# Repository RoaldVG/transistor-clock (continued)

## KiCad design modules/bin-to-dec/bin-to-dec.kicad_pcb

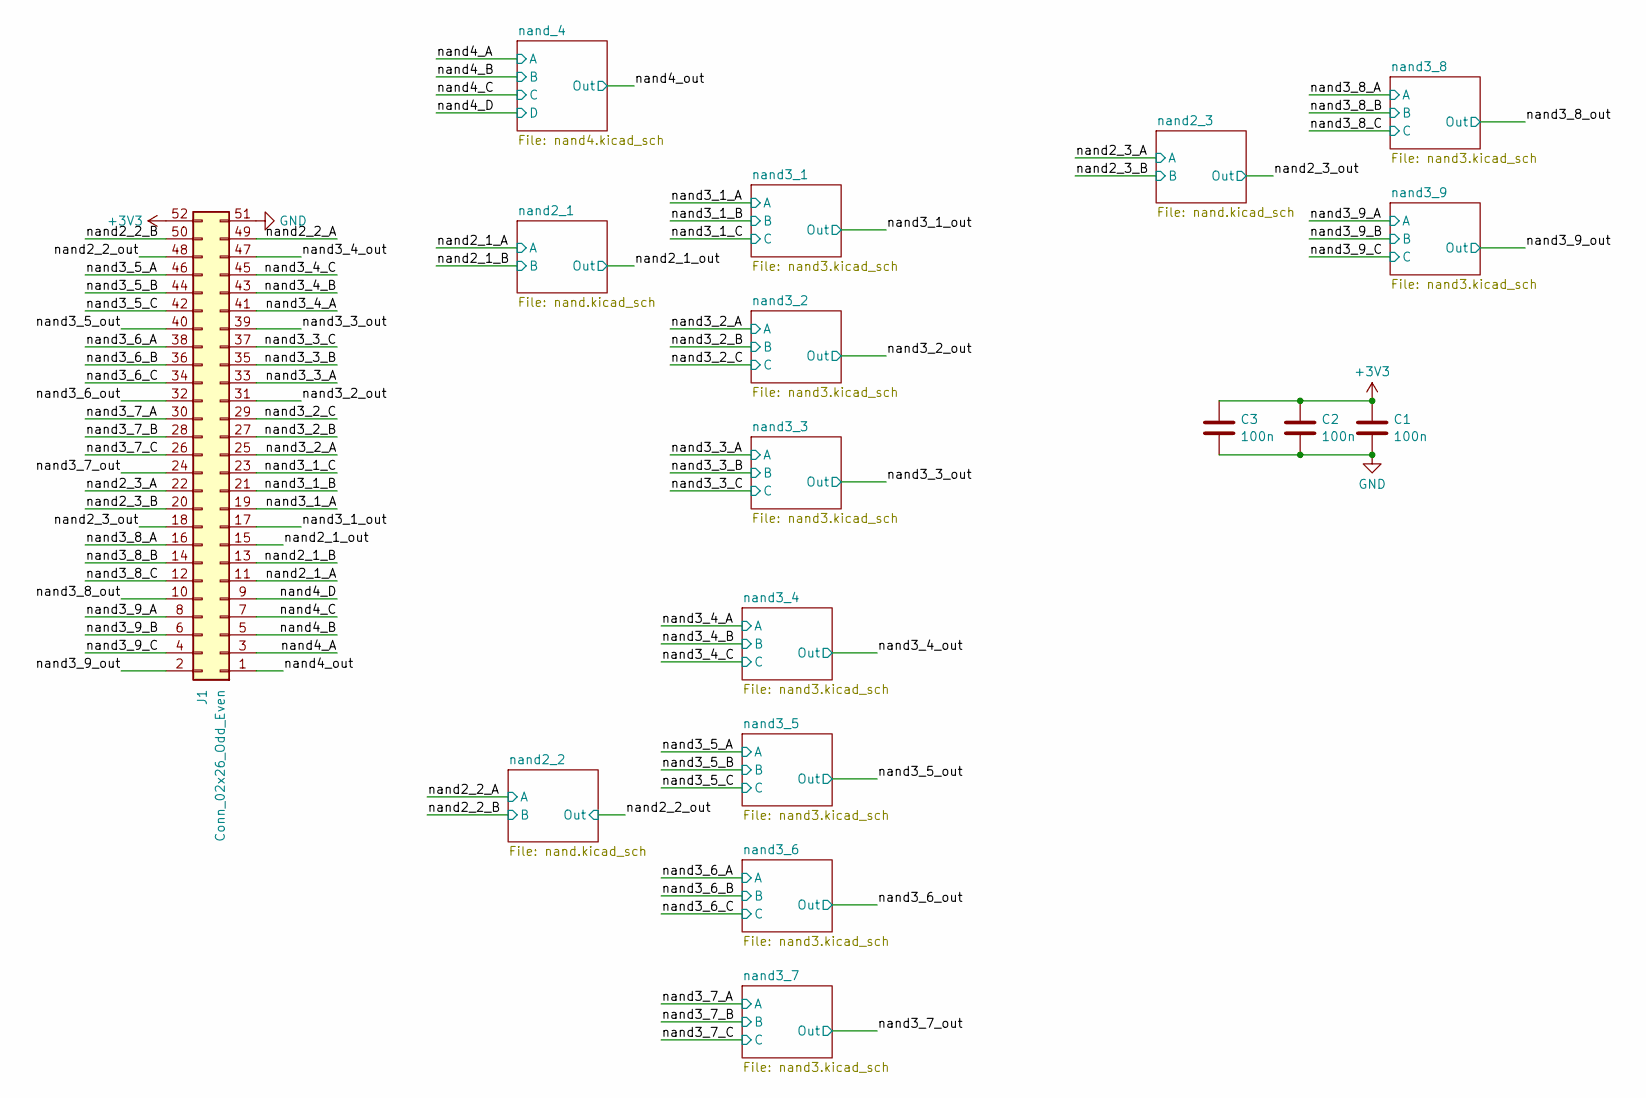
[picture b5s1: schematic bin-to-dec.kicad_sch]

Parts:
C1, C2, C3: 100n; C_0603_1608Metric; LCSC Part # C14663
J1: Conn_02x26_Odd_Even; mpcie-full-card

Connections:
+3V3: C1.1, C2.1, C3.1, J1.52; also elsewhere on the board
/nand2_1_A: J1.11; also elsewhere on the board
/nand2_1_B: J1.13; also elsewhere on the board
/nand2_1_out: J1.15; also elsewhere on the board
/nand2_2_A: J1.49; also elsewhere on the board
/nand2_2_B: J1.50; also elsewhere on the board
/nand2_2_out: J1.48; also elsewhere on the board
/nand2_3_A: J1.22; also elsewhere on the board
/nand2_3_B: J1.20; also elsewhere on the board
/nand2_3_out: J1.18; also elsewhere on the board
/nand3_1_A: J1.19; also elsewhere on the board
/nand3_1_B: J1.21; also elsewhere on the board
/nand3_1_C: J1.23; also elsewhere on the board
/nand3_1_out: J1.17; also elsewhere on the board
/nand3_2_A: J1.25; also elsewhere on the board
/nand3_2_B: J1.27; also elsewhere on the board
/nand3_2_C: J1.29; also elsewhere on the board
/nand3_2_out: J1.31; also elsewhere on the board
/nand3_3_A: J1.33; also elsewhere on the board
/nand3_3_B: J1.35; also elsewhere on the board
/nand3_3_C: J1.37; also elsewhere on the board
/nand3_3_out: J1.39; also elsewhere on the board
/nand3_4_A: J1.41; also elsewhere on the board
/nand3_4_B: J1.43; also elsewhere on the board
/nand3_4_C: J1.45; also elsewhere on the board
/nand3_4_out: J1.47; also elsewhere on the board
/nand3_5_A: J1.46; also elsewhere on the board
/nand3_5_B: J1.44; also elsewhere on the board
/nand3_5_C: J1.42; also elsewhere on the board
/nand3_5_out: J1.40; also elsewhere on the board
/nand3_6_A: J1.38; also elsewhere on the board
/nand3_6_B: J1.36; also elsewhere on the board
/nand3_6_C: J1.34; also elsewhere on the board
/nand3_6_out: J1.32; also elsewhere on the board
/nand3_7_A: J1.30; also elsewhere on the board
/nand3_7_B: J1.28; also elsewhere on the board
/nand3_7_C: J1.26; also elsewhere on the board
/nand3_7_out: J1.24; also elsewhere on the board
/nand3_8_A: J1.16; also elsewhere on the board
/nand3_8_B: J1.14; also elsewhere on the board
/nand3_8_C: J1.12; also elsewhere on the board
/nand3_8_out: J1.10; also elsewhere on the board
/nand3_9_A: J1.8; also elsewhere on the board
/nand3_9_B: J1.6; also elsewhere on the board
/nand3_9_C: J1.4; also elsewhere on the board
/nand3_9_out: J1.2; also elsewhere on the board
/nand4_A: J1.3; also elsewhere on the board
/nand4_B: J1.5; also elsewhere on the board
/nand4_C: J1.7; also elsewhere on the board
/nand4_D: J1.9; also elsewhere on the board
/nand4_out: J1.1; also elsewhere on the board
GND: C1.2, C2.2, C3.2, J1.51; also elsewhere on the board

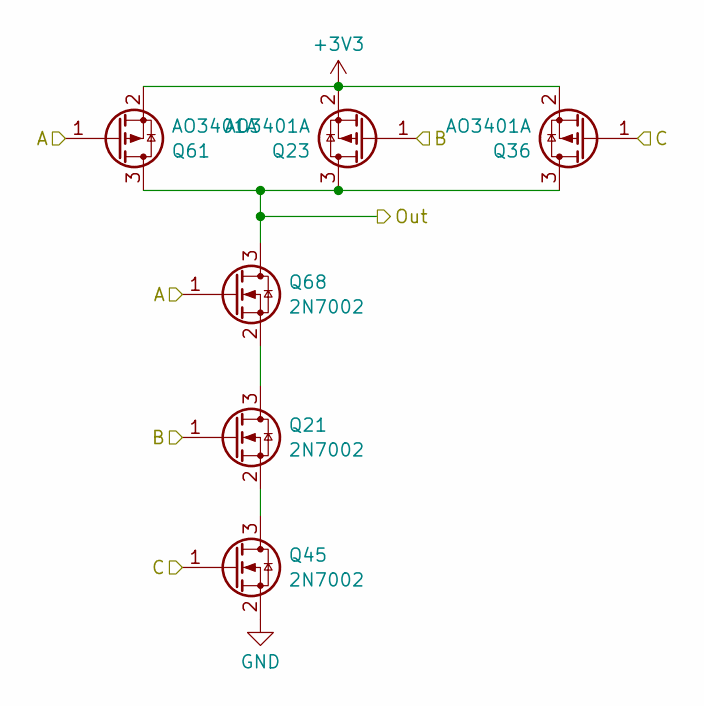
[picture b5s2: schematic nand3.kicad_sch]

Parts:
Q21, Q45, Q68: 2N7002; SOT-23; LCSC Part # C8545
Q23, Q36, Q61: AO3401A; SOT-23; LCSC Part # C15127

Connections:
+3V3: Q23.2 (S), Q36.2 (S), Q61.2 (S); also elsewhere on the board
/nand3_1_A: Q61.1 (G), Q68.1 (G); also elsewhere on the board
/nand3_1_B: Q21.1 (G), Q23.1 (G); also elsewhere on the board
/nand3_1_C: Q36.1 (G), Q45.1 (G); also elsewhere on the board
/nand3_1_out: Q23.3 (D), Q36.3 (D), Q61.3 (D), Q68.3 (D); also elsewhere on the board
GND: Q45.2 (S); also elsewhere on the board
unnamed: Q21.3 (D), Q68.2 (S)
unnamed: Q21.2 (S), Q45.3 (D)

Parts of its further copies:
Q1, Q4, Q9, Q10, Q11, Q14, Q20, Q28, Q29, Q30, Q31, Q32, Q38, Q39, Q40, Q42, Q43, Q48, Q49, Q60, Q63, Q69, Q71, Q73: 2N7002; SOT-23; LCSC Part # C8545
Q2, Q3, Q5, Q13, Q15, Q17, Q22, Q24, Q33, Q34, Q35, Q37, Q41, Q44, Q47, Q52, Q62, Q64, Q65, Q66, Q67, Q70, Q72, Q74: AO3401A; SOT-23; LCSC Part # C15127

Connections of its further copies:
+3V3: Q2.2 (S), Q3.2 (S), Q5.2 (S), Q13.2 (S), Q15.2 (S), Q17.2 (S), Q22.2 (S), Q24.2 (S), Q33.2 (S), Q34.2 (S), Q35.2 (S), Q37.2 (S), Q41.2 (S), Q44.2 (S), Q47.2 (S), Q52.2 (S), Q62.2 (S), Q64.2 (S), Q65.2 (S), Q66.2 (S), Q67.2 (S), Q70.2 (S), Q72.2 (S), Q74.2 (S); also elsewhere on the board
/nand3_2_A: Q35.1 (G), Q43.1 (G); also elsewhere on the board
/nand3_2_B: Q38.1 (G), Q41.1 (G); also elsewhere on the board
/nand3_2_C: Q37.1 (G), Q40.1 (G); also elsewhere on the board
/nand3_2_out: Q35.3 (D), Q37.3 (D), Q41.3 (D), Q43.3 (D); also elsewhere on the board
/nand3_3_A: Q4.1 (G), Q13.1 (G); also elsewhere on the board
/nand3_3_B: Q14.1 (G), Q17.1 (G); also elsewhere on the board
/nand3_3_C: Q9.1 (G), Q15.1 (G); also elsewhere on the board
/nand3_3_out: Q4.3 (D), Q13.3 (D), Q15.3 (D), Q17.3 (D); also elsewhere on the board
/nand3_4_A: Q3.1 (G), Q11.1 (G); also elsewhere on the board
/nand3_4_B: Q5.1 (G), Q10.1 (G); also elsewhere on the board
/nand3_4_C: Q1.1 (G), Q2.1 (G); also elsewhere on the board
/nand3_4_out: Q2.3 (D), Q3.3 (D), Q5.3 (D), Q11.3 (D); also elsewhere on the board
/nand3_5_A: Q39.1 (G), Q44.1 (G); also elsewhere on the board
/nand3_5_B: Q34.1 (G), Q42.1 (G); also elsewhere on the board
/nand3_5_C: Q48.1 (G), Q52.1 (G); also elsewhere on the board
/nand3_5_out: Q34.3 (D), Q39.3 (D), Q44.3 (D), Q52.3 (D); also elsewhere on the board
/nand3_6_A: Q29.1 (G), Q33.1 (G); also elsewhere on the board
/nand3_6_B: Q22.1 (G), Q28.1 (G); also elsewhere on the board
/nand3_6_C: Q20.1 (G), Q24.1 (G); also elsewhere on the board
/nand3_6_out: Q22.3 (D), Q24.3 (D), Q29.3 (D), Q33.3 (D); also elsewhere on the board
/nand3_7_A: Q32.1 (G), Q70.1 (G); also elsewhere on the board
/nand3_7_B: Q31.1 (G), Q64.1 (G); also elsewhere on the board
/nand3_7_C: Q30.1 (G), Q62.1 (G); also elsewhere on the board
/nand3_7_out: Q32.3 (D), Q62.3 (D), Q64.3 (D), Q70.3 (D); also elsewhere on the board
/nand3_8_A: Q47.1 (G), Q49.1 (G); also elsewhere on the board
/nand3_8_B: Q73.1 (G), Q74.1 (G); also elsewhere on the board
/nand3_8_C: Q71.1 (G), Q72.1 (G); also elsewhere on the board
/nand3_8_out: Q47.3 (D), Q49.3 (D), Q72.3 (D), Q74.3 (D); also elsewhere on the board
/nand3_9_A: Q63.1 (G), Q67.1 (G); also elsewhere on the board
/nand3_9_B: Q65.1 (G), Q69.1 (G); also elsewhere on the board
/nand3_9_C: Q60.1 (G), Q66.1 (G); also elsewhere on the board
/nand3_9_out: Q63.3 (D), Q65.3 (D), Q66.3 (D), Q67.3 (D); also elsewhere on the board
GND: Q1.2 (S), Q9.2 (S), Q20.2 (S), Q30.2 (S), Q40.2 (S), Q48.2 (S), Q60.2 (S), Q71.2 (S); also elsewhere on the board
unnamed: Q1.3 (D), Q10.2 (S)
unnamed: Q10.3 (D), Q11.2 (S)
unnamed: Q4.2 (S), Q14.3 (D)
unnamed: Q9.3 (D), Q14.2 (S)
unnamed: Q20.3 (D), Q28.2 (S)
unnamed: Q28.3 (D), Q29.2 (S)
unnamed: Q30.3 (D), Q31.2 (S)
unnamed: Q31.3 (D), Q32.2 (S)
unnamed: Q38.3 (D), Q43.2 (S)
unnamed: Q38.2 (S), Q40.3 (D)
unnamed: Q39.2 (S), Q42.3 (D)
unnamed: Q42.2 (S), Q48.3 (D)
unnamed: Q49.2 (S), Q73.3 (D)
unnamed: Q60.3 (D), Q69.2 (S)
unnamed: Q63.2 (S), Q69.3 (D)
unnamed: Q71.3 (D), Q73.2 (S)

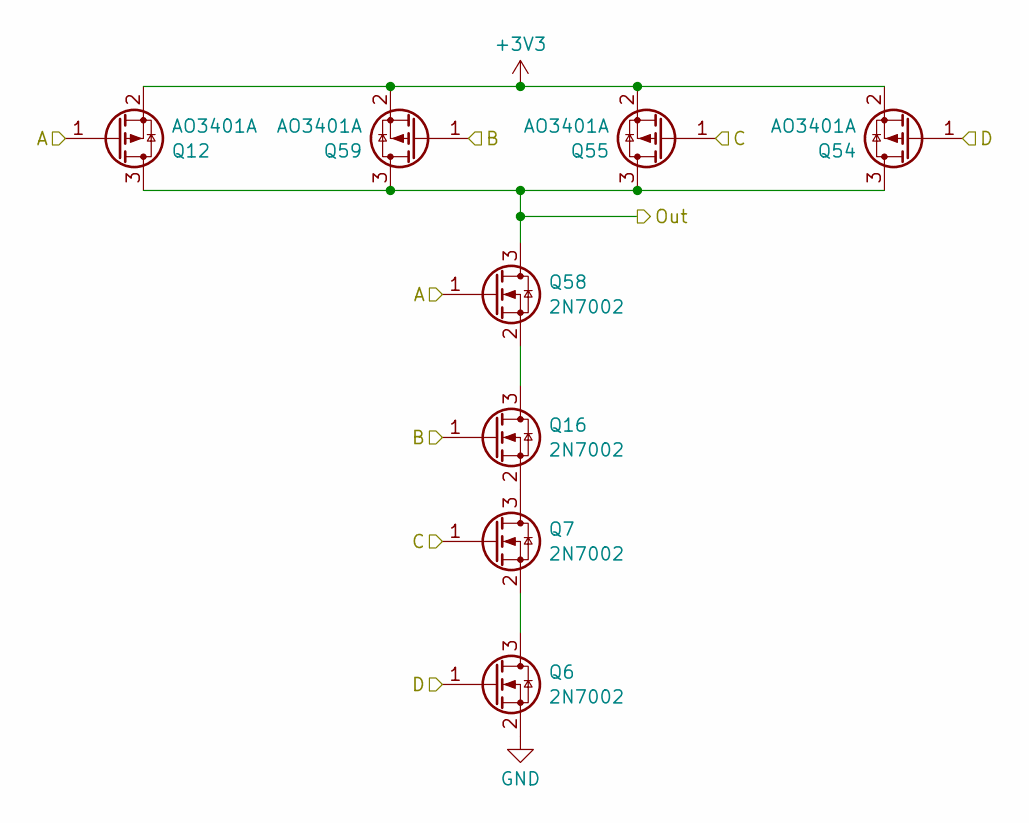
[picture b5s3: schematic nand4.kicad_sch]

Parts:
Q6, Q7, Q16, Q58: 2N7002; SOT-23; LCSC Part # C8545
Q12, Q54, Q55, Q59: AO3401A; SOT-23; LCSC Part # C15127

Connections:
+3V3: Q12.2 (S), Q54.2 (S), Q55.2 (S), Q59.2 (S); also elsewhere on the board
/nand4_A: Q12.1 (G), Q58.1 (G); also elsewhere on the board
/nand4_B: Q16.1 (G), Q59.1 (G); also elsewhere on the board
/nand4_C: Q7.1 (G), Q55.1 (G); also elsewhere on the board
/nand4_D: Q6.1 (G), Q54.1 (G); also elsewhere on the board
/nand4_out: Q12.3 (D), Q54.3 (D), Q55.3 (D), Q58.3 (D), Q59.3 (D); also elsewhere on the board
GND: Q6.2 (S); also elsewhere on the board
unnamed: Q6.3 (D), Q7.2 (S)
unnamed: Q16.3 (D), Q58.2 (S)
unnamed: Q7.3 (D), Q16.2 (S)

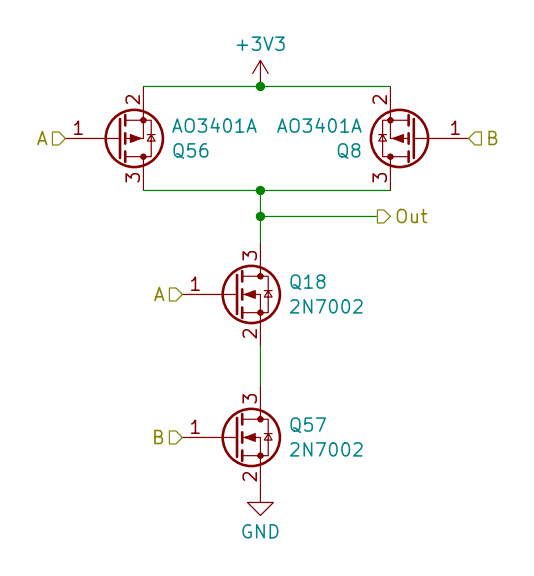
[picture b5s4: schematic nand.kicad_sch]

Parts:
Q8, Q56: AO3401A; SOT-23; LCSC Part # C15127
Q18, Q57: 2N7002; SOT-23; LCSC Part # C8545

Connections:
+3V3: Q8.2 (S), Q56.2 (S); also elsewhere on the board
/nand2_1_A: Q18.1 (G), Q56.1 (G); also elsewhere on the board
/nand2_1_B: Q8.1 (G), Q57.1 (G); also elsewhere on the board
/nand2_1_out: Q8.3 (D), Q18.3 (D), Q56.3 (D); also elsewhere on the board
GND: Q57.2 (S); also elsewhere on the board
unnamed: Q18.2 (S), Q57.3 (D)

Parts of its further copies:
Q19, Q25, Q46, Q51: 2N7002; SOT-23; LCSC Part # C8545
Q26, Q27, Q50, Q53: AO3401A; SOT-23; LCSC Part # C15127

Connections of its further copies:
+3V3: Q26.2 (S), Q27.2 (S), Q50.2 (S), Q53.2 (S); also elsewhere on the board
/nand2_2_A: Q25.1 (G), Q26.1 (G); also elsewhere on the board
/nand2_2_B: Q19.1 (G), Q27.1 (G); also elsewhere on the board
/nand2_2_out: Q25.3 (D), Q26.3 (D), Q27.3 (D); also elsewhere on the board
/nand2_3_A: Q51.1 (G), Q53.1 (G); also elsewhere on the board
/nand2_3_B: Q46.1 (G), Q50.1 (G); also elsewhere on the board
/nand2_3_out: Q50.3 (D), Q51.3 (D), Q53.3 (D); also elsewhere on the board
GND: Q19.2 (S), Q46.2 (S); also elsewhere on the board
unnamed: Q19.3 (D), Q25.2 (S)
unnamed: Q46.3 (D), Q51.2 (S)

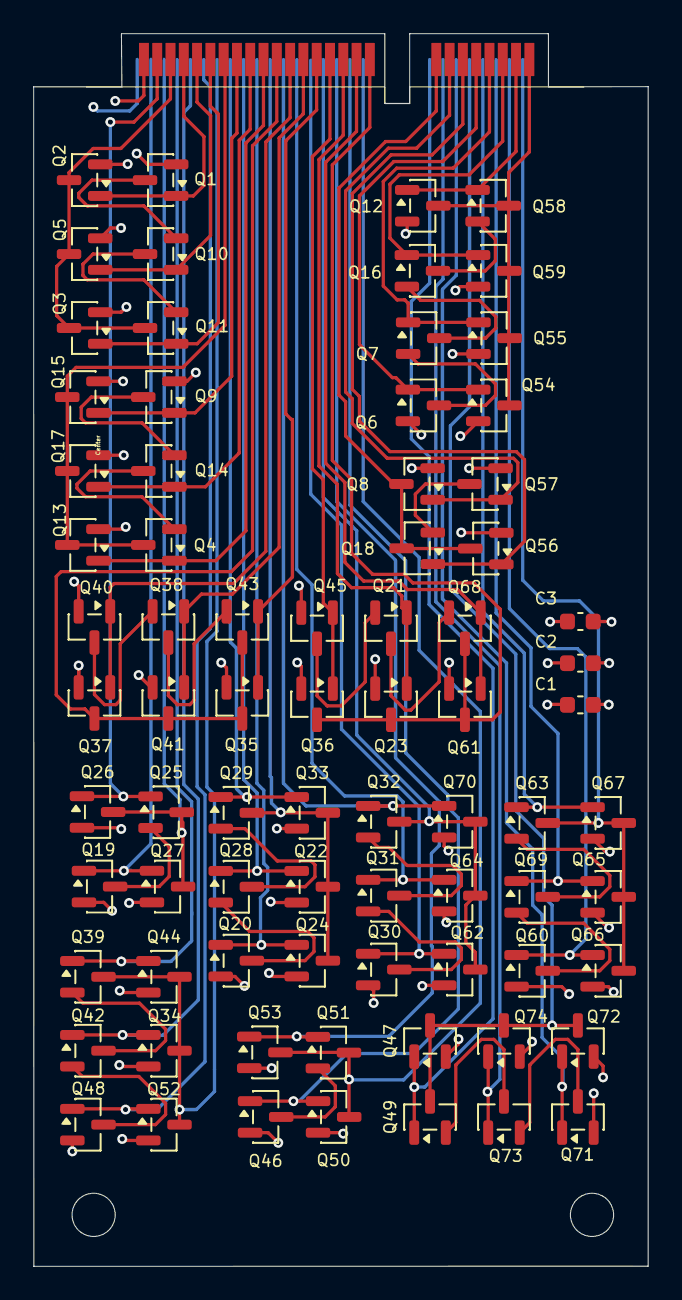
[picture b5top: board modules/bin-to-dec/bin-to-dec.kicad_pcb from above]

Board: 4 copper layers, 37.0 x 74.2 mm, 78 parts (0 on the bottom side), 76 nets.

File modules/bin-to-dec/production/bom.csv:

Designator,Footprint,Quantity,Value,LCSC Part #
"C1, C2, C3",0603,3,100n,C14663
"Q1, Q10, Q11, Q14, Q16, Q18, Q19, Q20, Q21, Q25, Q28, Q29, Q30, Q31, Q32, Q38, Q39, Q4, Q40, Q42, Q43, Q45, Q46, Q48, Q49, Q51, Q57, Q58, Q6, Q60, Q63, Q68, Q69, Q7, Q71, Q73, Q9",SOT-23,37,2N7002,C8545
"Q12, Q13, Q15, Q17, Q2, Q22, Q23, Q24, Q26, Q27, Q3, Q33, Q34, Q35, Q36, Q37, Q41, Q44, Q47, Q5, Q50, Q52, Q53, Q54, Q55, Q56, Q59, Q61, Q62, Q64, Q65, Q66, Q67, Q70, Q72, Q74, Q8",SOT-23,37,AO3401A,C15127

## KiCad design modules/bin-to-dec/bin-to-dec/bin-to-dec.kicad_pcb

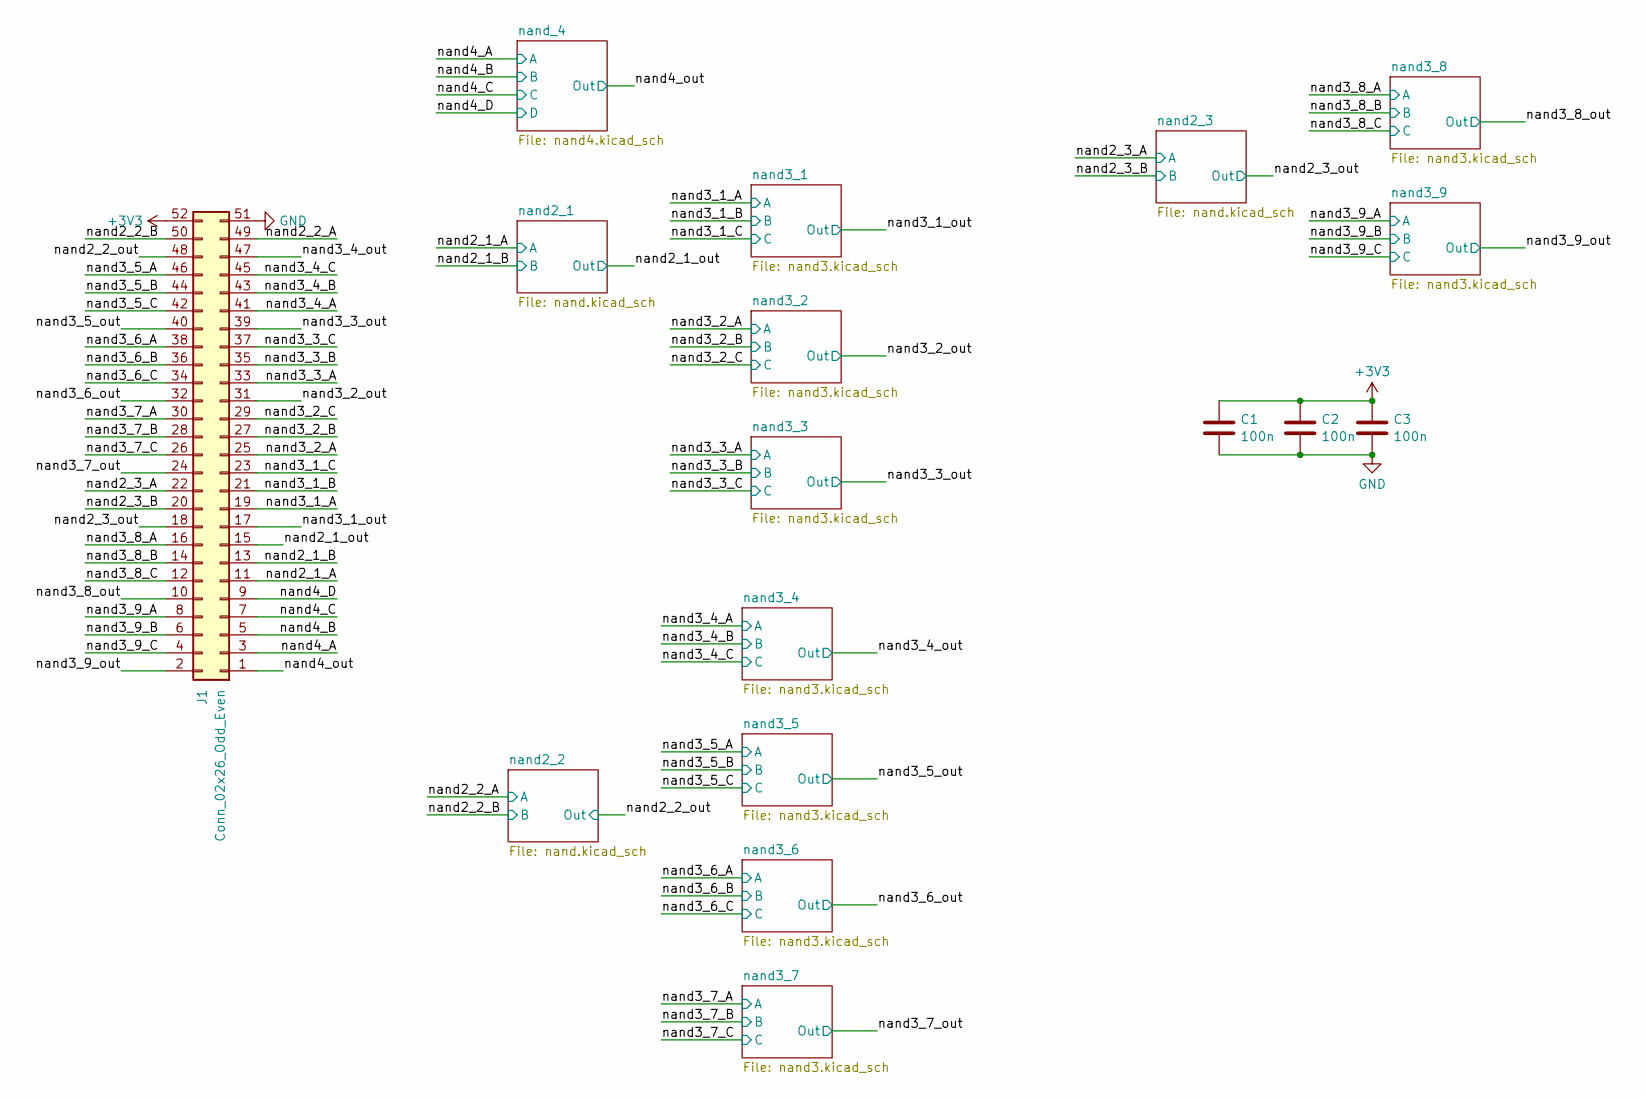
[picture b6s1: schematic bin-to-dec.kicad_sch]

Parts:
C1, C2, C3: 100n; C_0603_1608Metric
J1: Conn_02x26_Odd_Even; mpcie-full-card

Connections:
+3V3: C1.1, C2.1, C3.1, J1.52; also elsewhere on the board
/nand2_1_A: J1.11; also elsewhere on the board
/nand2_1_B: J1.13; also elsewhere on the board
/nand2_1_out: J1.15; also elsewhere on the board
/nand2_2_A: J1.49; also elsewhere on the board
/nand2_2_B: J1.50; also elsewhere on the board
/nand2_2_out: J1.48; also elsewhere on the board
/nand2_3_A: J1.22; also elsewhere on the board
/nand2_3_B: J1.20; also elsewhere on the board
/nand2_3_out: J1.18; also elsewhere on the board
/nand3_1_A: J1.19; also elsewhere on the board
/nand3_1_B: J1.21; also elsewhere on the board
/nand3_1_C: J1.23; also elsewhere on the board
/nand3_1_out: J1.17; also elsewhere on the board
/nand3_2_A: J1.25; also elsewhere on the board
/nand3_2_B: J1.27; also elsewhere on the board
/nand3_2_C: J1.29; also elsewhere on the board
/nand3_2_out: J1.31; also elsewhere on the board
/nand3_3_A: J1.33; also elsewhere on the board
/nand3_3_B: J1.35; also elsewhere on the board
/nand3_3_C: J1.37; also elsewhere on the board
/nand3_3_out: J1.39; also elsewhere on the board
/nand3_4_A: J1.41; also elsewhere on the board
/nand3_4_B: J1.43; also elsewhere on the board
/nand3_4_C: J1.45; also elsewhere on the board
/nand3_4_out: J1.47; also elsewhere on the board
/nand3_5_A: J1.46; also elsewhere on the board
/nand3_5_B: J1.44; also elsewhere on the board
/nand3_5_C: J1.42; also elsewhere on the board
/nand3_5_out: J1.40; also elsewhere on the board
/nand3_6_A: J1.38; also elsewhere on the board
/nand3_6_B: J1.36; also elsewhere on the board
/nand3_6_C: J1.34; also elsewhere on the board
/nand3_6_out: J1.32; also elsewhere on the board
/nand3_7_A: J1.30; also elsewhere on the board
/nand3_7_B: J1.28; also elsewhere on the board
/nand3_7_C: J1.26; also elsewhere on the board
/nand3_7_out: J1.24; also elsewhere on the board
/nand3_8_A: J1.16; also elsewhere on the board
/nand3_8_B: J1.14; also elsewhere on the board
/nand3_8_C: J1.12; also elsewhere on the board
/nand3_8_out: J1.10; also elsewhere on the board
/nand3_9_A: J1.8; also elsewhere on the board
/nand3_9_B: J1.6; also elsewhere on the board
/nand3_9_C: J1.4; also elsewhere on the board
/nand3_9_out: J1.2; also elsewhere on the board
/nand4_A: J1.3; also elsewhere on the board
/nand4_B: J1.5; also elsewhere on the board
/nand4_C: J1.7; also elsewhere on the board
/nand4_D: J1.9; also elsewhere on the board
/nand4_out: J1.1; also elsewhere on the board
GND: C1.2, C2.2, C3.2, J1.51; also elsewhere on the board

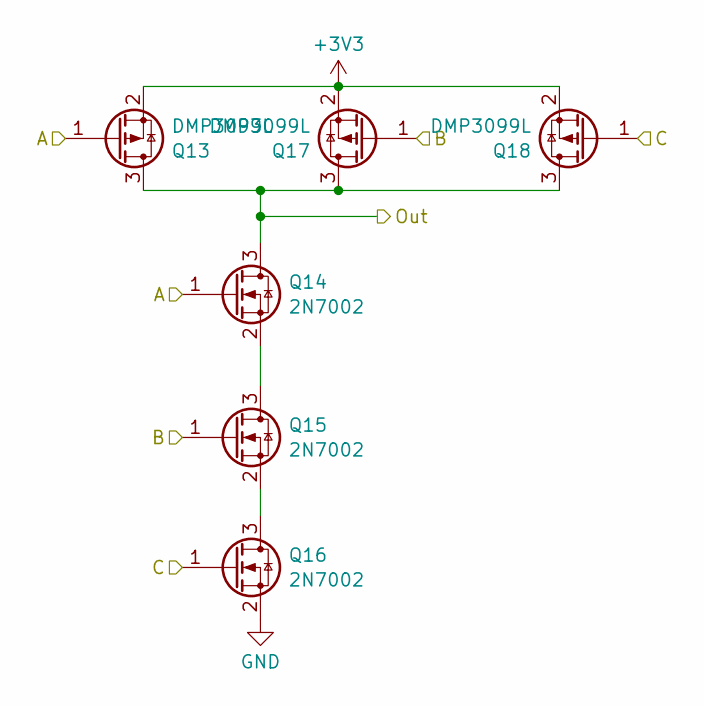
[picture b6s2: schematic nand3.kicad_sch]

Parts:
Q13, Q17, Q18: DMP3099L; SOT-23
Q14, Q15, Q16: 2N7002; SOT-23

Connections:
+3V3: Q13.2 (S), Q17.2 (S), Q18.2 (S); also elsewhere on the board
/nand3_1_A: Q13.1 (G), Q14.1 (G); also elsewhere on the board
/nand3_1_B: Q15.1 (G), Q17.1 (G); also elsewhere on the board
/nand3_1_C: Q16.1 (G), Q18.1 (G); also elsewhere on the board
/nand3_1_out: Q13.3 (D), Q14.3 (D), Q17.3 (D), Q18.3 (D); also elsewhere on the board
GND: Q16.2 (S); also elsewhere on the board
unnamed: Q14.2 (S), Q15.3 (D)
unnamed: Q15.2 (S), Q16.3 (D)

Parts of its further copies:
Q19, Q23, Q24, Q25, Q29, Q30, Q35, Q39, Q40, Q41, Q45, Q46, Q47, Q51, Q52, Q53, Q57, Q58, Q63, Q67, Q68, Q69, Q73, Q74: DMP3099L; SOT-23
Q20, Q21, Q22, Q26, Q27, Q28, Q36, Q37, Q38, Q42, Q43, Q44, Q48, Q49, Q50, Q54, Q55, Q56, Q64, Q65, Q66, Q70, Q71, Q72: 2N7002; SOT-23

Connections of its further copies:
+3V3: Q19.2 (S), Q23.2 (S), Q24.2 (S), Q25.2 (S), Q29.2 (S), Q30.2 (S), Q35.2 (S), Q39.2 (S), Q40.2 (S), Q41.2 (S), Q45.2 (S), Q46.2 (S), Q47.2 (S), Q51.2 (S), Q52.2 (S), Q53.2 (S), Q57.2 (S), Q58.2 (S), Q63.2 (S), Q67.2 (S), Q68.2 (S), Q69.2 (S), Q73.2 (S), Q74.2 (S); also elsewhere on the board
/nand3_2_A: Q19.1 (G), Q20.1 (G); also elsewhere on the board
/nand3_2_B: Q21.1 (G), Q23.1 (G); also elsewhere on the board
/nand3_2_C: Q22.1 (G), Q24.1 (G); also elsewhere on the board
/nand3_2_out: Q19.3 (D), Q20.3 (D), Q23.3 (D), Q24.3 (D); also elsewhere on the board
/nand3_3_A: Q25.1 (G), Q26.1 (G); also elsewhere on the board
/nand3_3_B: Q27.1 (G), Q29.1 (G); also elsewhere on the board
/nand3_3_C: Q28.1 (G), Q30.1 (G); also elsewhere on the board
/nand3_3_out: Q25.3 (D), Q26.3 (D), Q29.3 (D), Q30.3 (D); also elsewhere on the board
/nand3_4_A: Q53.1 (G), Q54.1 (G); also elsewhere on the board
/nand3_4_B: Q55.1 (G), Q57.1 (G); also elsewhere on the board
/nand3_4_C: Q56.1 (G), Q58.1 (G); also elsewhere on the board
/nand3_4_out: Q53.3 (D), Q54.3 (D), Q57.3 (D), Q58.3 (D); also elsewhere on the board
/nand3_5_A: Q35.1 (G), Q36.1 (G); also elsewhere on the board
/nand3_5_B: Q37.1 (G), Q39.1 (G); also elsewhere on the board
/nand3_5_C: Q38.1 (G), Q40.1 (G); also elsewhere on the board
/nand3_5_out: Q35.3 (D), Q36.3 (D), Q39.3 (D), Q40.3 (D); also elsewhere on the board
/nand3_6_A: Q41.1 (G), Q42.1 (G); also elsewhere on the board
/nand3_6_B: Q43.1 (G), Q45.1 (G); also elsewhere on the board
/nand3_6_C: Q44.1 (G), Q46.1 (G); also elsewhere on the board
/nand3_6_out: Q41.3 (D), Q42.3 (D), Q45.3 (D), Q46.3 (D); also elsewhere on the board
/nand3_7_A: Q47.1 (G), Q48.1 (G); also elsewhere on the board
/nand3_7_B: Q49.1 (G), Q51.1 (G); also elsewhere on the board
/nand3_7_C: Q50.1 (G), Q52.1 (G); also elsewhere on the board
/nand3_7_out: Q47.3 (D), Q48.3 (D), Q51.3 (D), Q52.3 (D); also elsewhere on the board
/nand3_8_A: Q69.1 (G), Q70.1 (G); also elsewhere on the board
/nand3_8_B: Q71.1 (G), Q73.1 (G); also elsewhere on the board
/nand3_8_C: Q72.1 (G), Q74.1 (G); also elsewhere on the board
/nand3_8_out: Q69.3 (D), Q70.3 (D), Q73.3 (D), Q74.3 (D); also elsewhere on the board
/nand3_9_A: Q63.1 (G), Q64.1 (G); also elsewhere on the board
/nand3_9_B: Q65.1 (G), Q67.1 (G); also elsewhere on the board
/nand3_9_C: Q66.1 (G), Q68.1 (G); also elsewhere on the board
/nand3_9_out: Q63.3 (D), Q64.3 (D), Q67.3 (D), Q68.3 (D); also elsewhere on the board
GND: Q22.2 (S), Q28.2 (S), Q38.2 (S), Q44.2 (S), Q50.2 (S), Q56.2 (S), Q66.2 (S), Q72.2 (S); also elsewhere on the board
unnamed: Q20.2 (S), Q21.3 (D)
unnamed: Q21.2 (S), Q22.3 (D)
unnamed: Q26.2 (S), Q27.3 (D)
unnamed: Q27.2 (S), Q28.3 (D)
unnamed: Q36.2 (S), Q37.3 (D)
unnamed: Q37.2 (S), Q38.3 (D)
unnamed: Q42.2 (S), Q43.3 (D)
unnamed: Q43.2 (S), Q44.3 (D)
unnamed: Q48.2 (S), Q49.3 (D)
unnamed: Q49.2 (S), Q50.3 (D)
unnamed: Q54.2 (S), Q55.3 (D)
unnamed: Q55.2 (S), Q56.3 (D)
unnamed: Q64.2 (S), Q65.3 (D)
unnamed: Q65.2 (S), Q66.3 (D)
unnamed: Q70.2 (S), Q71.3 (D)
unnamed: Q71.2 (S), Q72.3 (D)

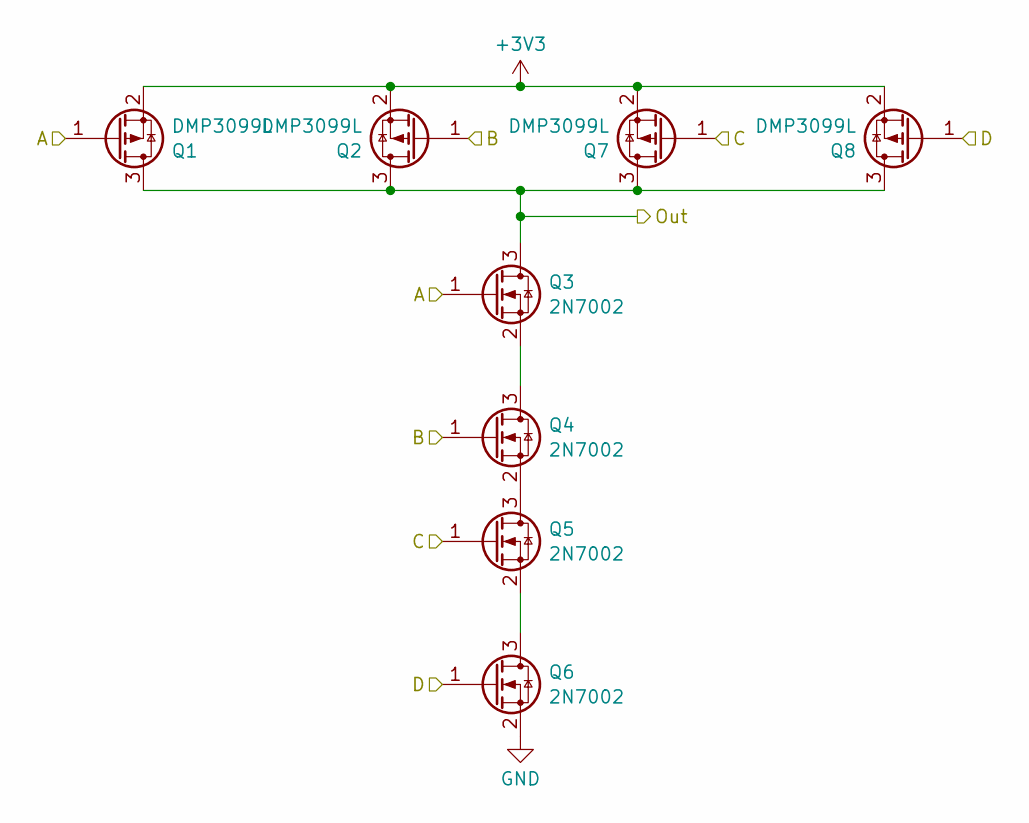
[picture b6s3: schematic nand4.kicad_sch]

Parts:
Q1, Q2, Q7, Q8: DMP3099L; SOT-23
Q3, Q4, Q5, Q6: 2N7002; SOT-23

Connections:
+3V3: Q1.2 (S), Q2.2 (S), Q7.2 (S), Q8.2 (S); also elsewhere on the board
/nand4_A: Q1.1 (G), Q3.1 (G); also elsewhere on the board
/nand4_B: Q2.1 (G), Q4.1 (G); also elsewhere on the board
/nand4_C: Q5.1 (G), Q7.1 (G); also elsewhere on the board
/nand4_D: Q6.1 (G), Q8.1 (G); also elsewhere on the board
/nand4_out: Q1.3 (D), Q2.3 (D), Q3.3 (D), Q7.3 (D), Q8.3 (D); also elsewhere on the board
GND: Q6.2 (S); also elsewhere on the board
unnamed: Q3.2 (S), Q4.3 (D)
unnamed: Q4.2 (S), Q5.3 (D)
unnamed: Q5.2 (S), Q6.3 (D)

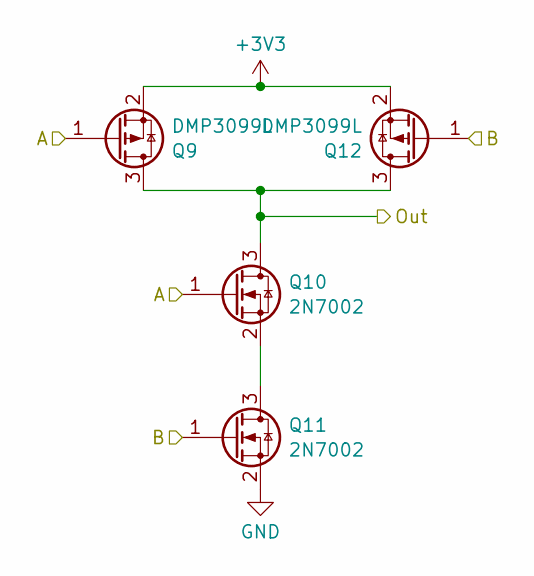
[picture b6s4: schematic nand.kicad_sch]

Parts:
Q9, Q12: DMP3099L; SOT-23
Q10, Q11: 2N7002; SOT-23

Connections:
+3V3: Q9.2 (S), Q12.2 (S); also elsewhere on the board
/nand2_1_A: Q9.1 (G), Q10.1 (G); also elsewhere on the board
/nand2_1_B: Q11.1 (G), Q12.1 (G); also elsewhere on the board
/nand2_1_out: Q9.3 (D), Q10.3 (D), Q12.3 (D); also elsewhere on the board
GND: Q11.2 (S); also elsewhere on the board
unnamed: Q10.2 (S), Q11.3 (D)

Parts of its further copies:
Q31, Q34, Q59, Q62: DMP3099L; SOT-23
Q32, Q33, Q60, Q61: 2N7002; SOT-23

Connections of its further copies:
+3V3: Q31.2 (S), Q34.2 (S), Q59.2 (S), Q62.2 (S); also elsewhere on the board
/nand2_2_A: Q31.1 (G), Q32.1 (G); also elsewhere on the board
/nand2_2_B: Q33.1 (G), Q34.1 (G); also elsewhere on the board
/nand2_2_out: Q31.3 (D), Q32.3 (D), Q34.3 (D); also elsewhere on the board
/nand2_3_A: Q59.1 (G), Q60.1 (G); also elsewhere on the board
/nand2_3_B: Q61.1 (G), Q62.1 (G); also elsewhere on the board
/nand2_3_out: Q59.3 (D), Q60.3 (D), Q62.3 (D); also elsewhere on the board
GND: Q33.2 (S), Q61.2 (S); also elsewhere on the board
unnamed: Q32.2 (S), Q33.3 (D)
unnamed: Q60.2 (S), Q61.3 (D)

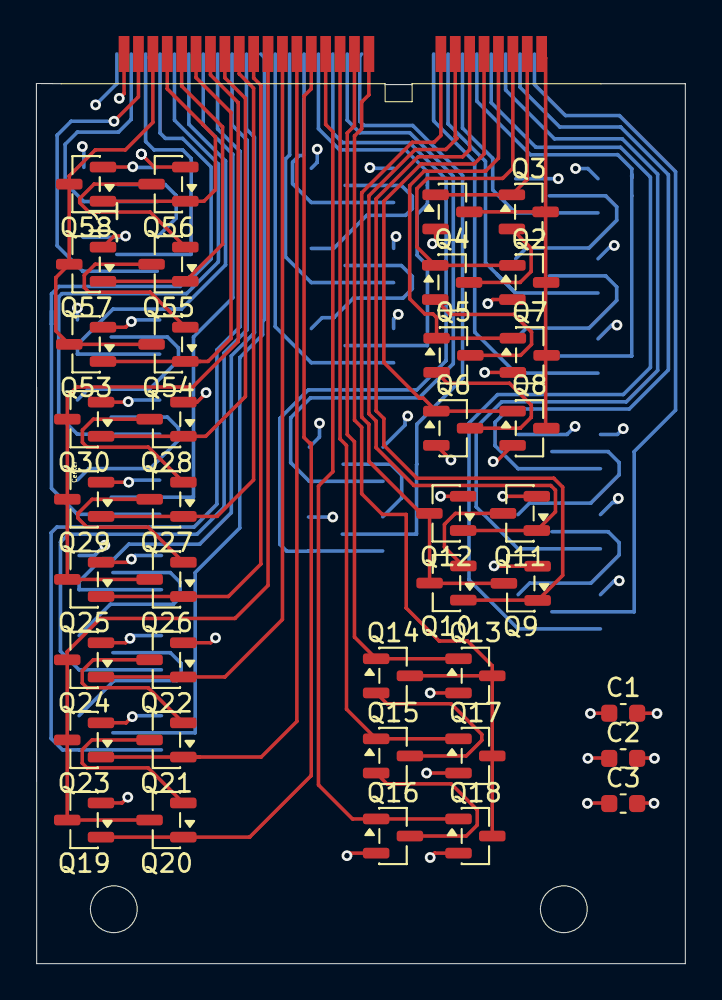
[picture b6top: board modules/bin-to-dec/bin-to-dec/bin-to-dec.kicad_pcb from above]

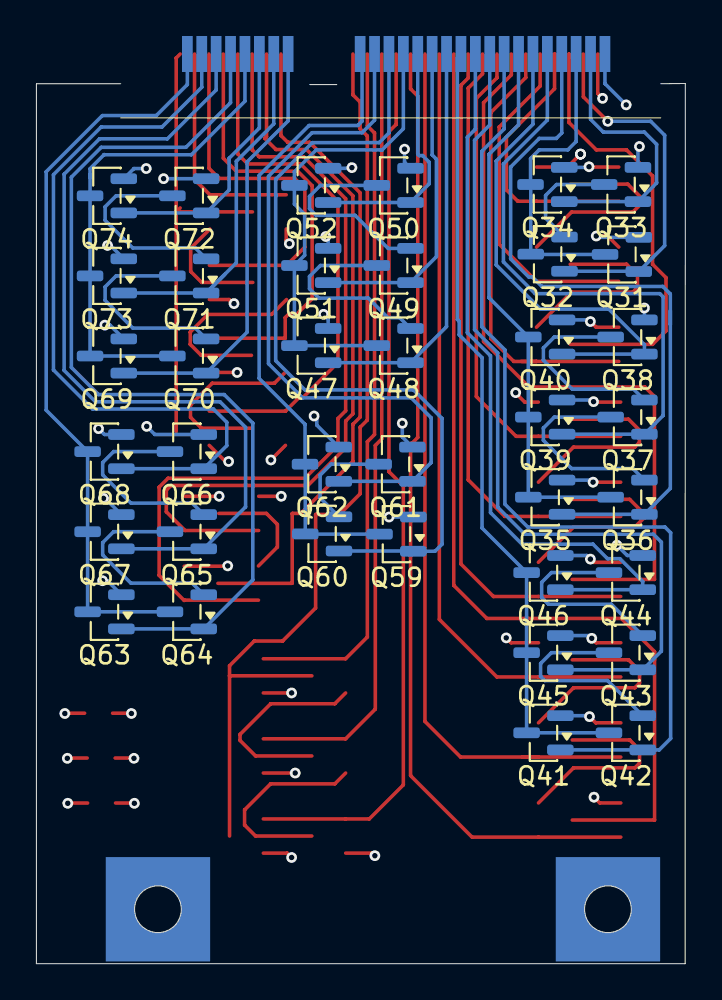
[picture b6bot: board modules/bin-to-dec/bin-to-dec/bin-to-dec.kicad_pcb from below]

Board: 4 copper layers, 36.1 x 48.9 mm, 78 parts (38 on the bottom side), 76 nets.
